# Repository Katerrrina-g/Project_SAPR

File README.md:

# Отчет по Домашнему заданию: Разработка печатной платы блока питания
**Выполнила: Генина Е.И.**
**Группа: БМТ2-31М**
**Дисциплина: САПР электронных стредств**
Среда разработки: KiCad 10.0

**1. Описание проекта**
В рамках данного проекта была разработана печатная плата блока питания. Устройство предназначено для питания электроимпедансного томографа для функциональной диагностики мышц.
На вход платы подается неразвязанное напряжение +5В (от внешнего источника питания, например, от ноутбука). С помощью рассматриваемой схемы генерируются следующие выходные напряжения:

+3.3В (для цифровых цепей);
+5В (развязанное для аналоговых цепей);
+15В и -15В (для аналоговых цепей).

Основу схемы составляют преобразователи и регуляторы напряжения:

ADP5071 — двухканальный DC-DC преобразователь с генерацией положительного и отрицательного напряжений.

ISOUSB211 — изолированный повторитель USB 2.0 (обеспечивает развязку).

TPS7A49 и TPS7A30 — малошумящие линейные регуляторы для формирования напряжений +15В и -15В.

**2. Библиотека компонентов и Git-сабмодуль**
Библиотека компонентов была вынесена в отдельный репозиторий и подключена к основному проекту как git-сабмодуль. Это обеспечивает независимое версионирование и переиспользование.

Символы (УГО): Файл UGO.kicad_sym. УГО оформлены по ГОСТ.

Посадочные места: Папка SAPR.pretty.

Партномеры: В свойствах каждого компонента заполнено поле Manufacturer_Part_Number с партномерами.

Пути: В настройках KiCad используются относительные пути с применением переменной ${KIPRJMOD} (${KIPRJMOD}/libs/kicad-library/UGO.kicad_sym;${KIPRJMOD}/libs/kicad-library/SAPR.pretty).

Все посадочные места были проверены на соответствие даташитам. Для стандартных компонентов (резисторы, конденсаторы) использовались стандартные футпринты, для специфических — специализированные из базы производителя, отстутствующие посадочные места были созданы самостоятельно. 3D-модели привязаны и корректно отображаются.

**3. Принципиальная схема (Э3)**
Схема электрическая принципиальная оформлена на листе формата А3 согласно ГОСТ.

Классы цепей: Был создан класс Power (фиолетовый цвет, стиль линии — штрихи). В этот класс включены все цепи питания. Остальные цепи относятся к классу Default.

Ширина дорожек для класса Power задана как 0.4 мм, однако при трассировке преимущественно использовались полигоны (зоны).

**4. Файл печатной платы**
Плата спроектирована в 4 слоя с учетом технологических ограничений производства «Резонит».

Стек слоев (Board Stackup):
F.Cu (Верхний слой) — 0.035 мм
Диэлектрик 1 (Prepreg) — 0.1 мм
In1.Cu (Внутренний 1) — 0.035 мм
Диэлектрик 2 (Ядро, FR4) — 1.24 мм
In2.Cu (Внутренний 2) — 0.035 мм
Диэлектрик 3 (Prepreg) — 0.1 мм
B.Cu (Нижний слой) — 0.035 мм

Технологические нормы (Constraints):
Minimum clearance (Мин. зазор)	0.20 мм

Copper to edge clearance (Зазор от меди до края) 0.50 мм

Minimum track width (Мин. ширина дорожки) 0.20 мм

Minimum annular width (Мин. кольцо меди) 0.15 мм

Minimum drill size (Мин. диаметр сверления)	0.30 мм

Hole to hole distance (Расстояние между отверстиями)	0.20 мм

Copper to hole clearance (Зазор медь-отверстие)	0.25 мм

Minimum text height (Мин. высота текста)	1.0 мм

Minimum text thickness (Мин. толщина линии)	0.15 мм

Silk to soldermask clearance (Зазор шелкография-маска)	0.10 мм

Soldermask expansion (Расширение маски)	0.05 мм

Minimum connection width (Мин. ширина соединения)	0.20 мм

Thermal relief spoke count (Кол-во спиц развязки)	4

Зазор медь-край платы: 0.4 мм

Использованы переходные отверстия диаметром 0,3/0.6 мм (со сверлом 0.3 мм).

**5. Автоматизация сборки**
Для автоматизации процесса проверки и подготовки производственных файлов в корне проекта (путь D:\Univ\САПР ЭС\Project_sapr) расположен скрипт build.bat.

Скрипт использует утилиту kicad-cli и выполняет следующие действия:

ERC — Проверка электрических правил схемы (учитывает предупреждения).

DRC — Проверка правил проектирования печатной платы (учитывает предупреждения).

Gerber + Excellon — Генерация файлов для производства.

BOM — Генерация перечня элементов в формате CSV.

PDF — Экспорт схемы в PDF.

**6. Инструкция по развертыванию проекта**
Для того чтобы скачать проект вместе с библиотекой, необходимо использовать следующую команду:

git clone --recursive https://github.com/Katerrrina-g/Project_SAPR.git

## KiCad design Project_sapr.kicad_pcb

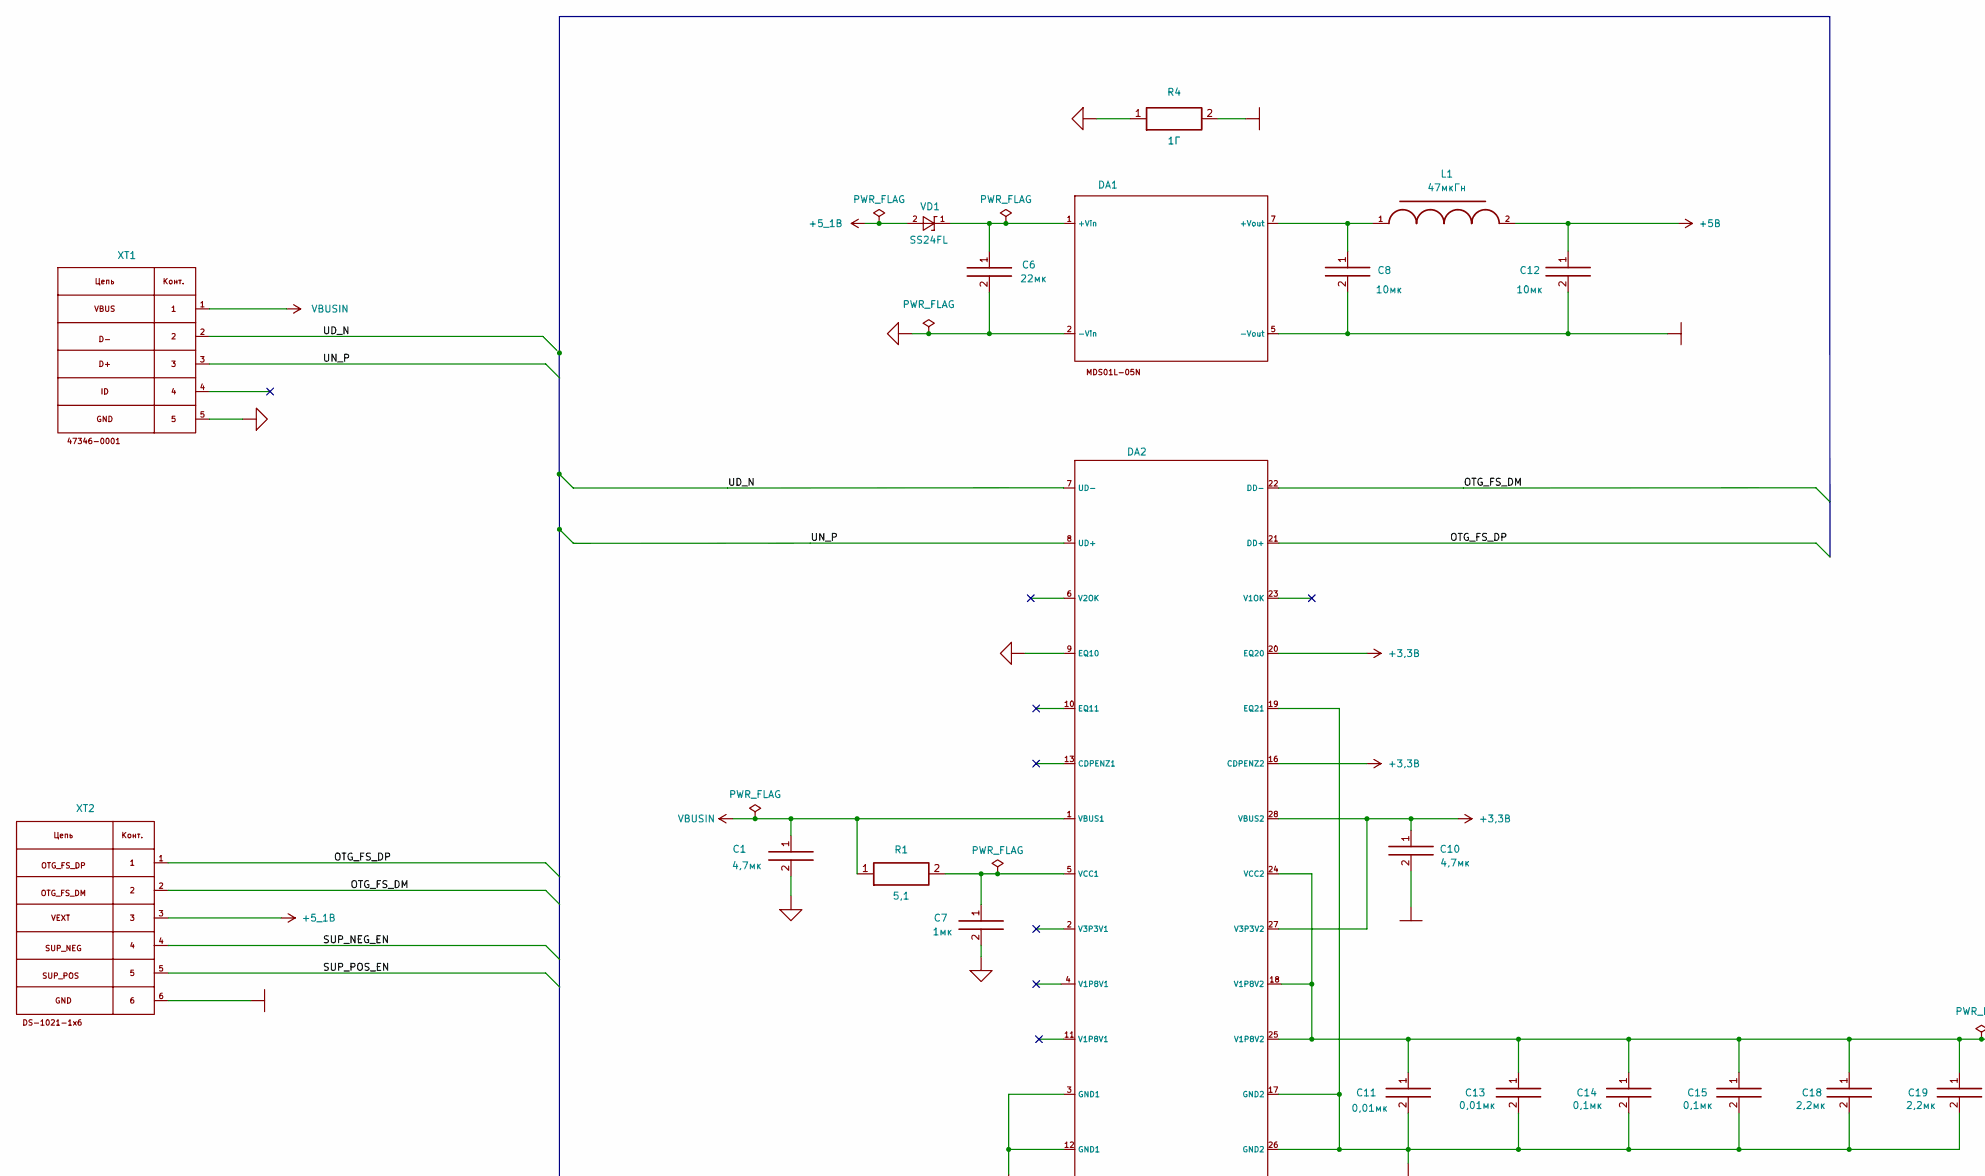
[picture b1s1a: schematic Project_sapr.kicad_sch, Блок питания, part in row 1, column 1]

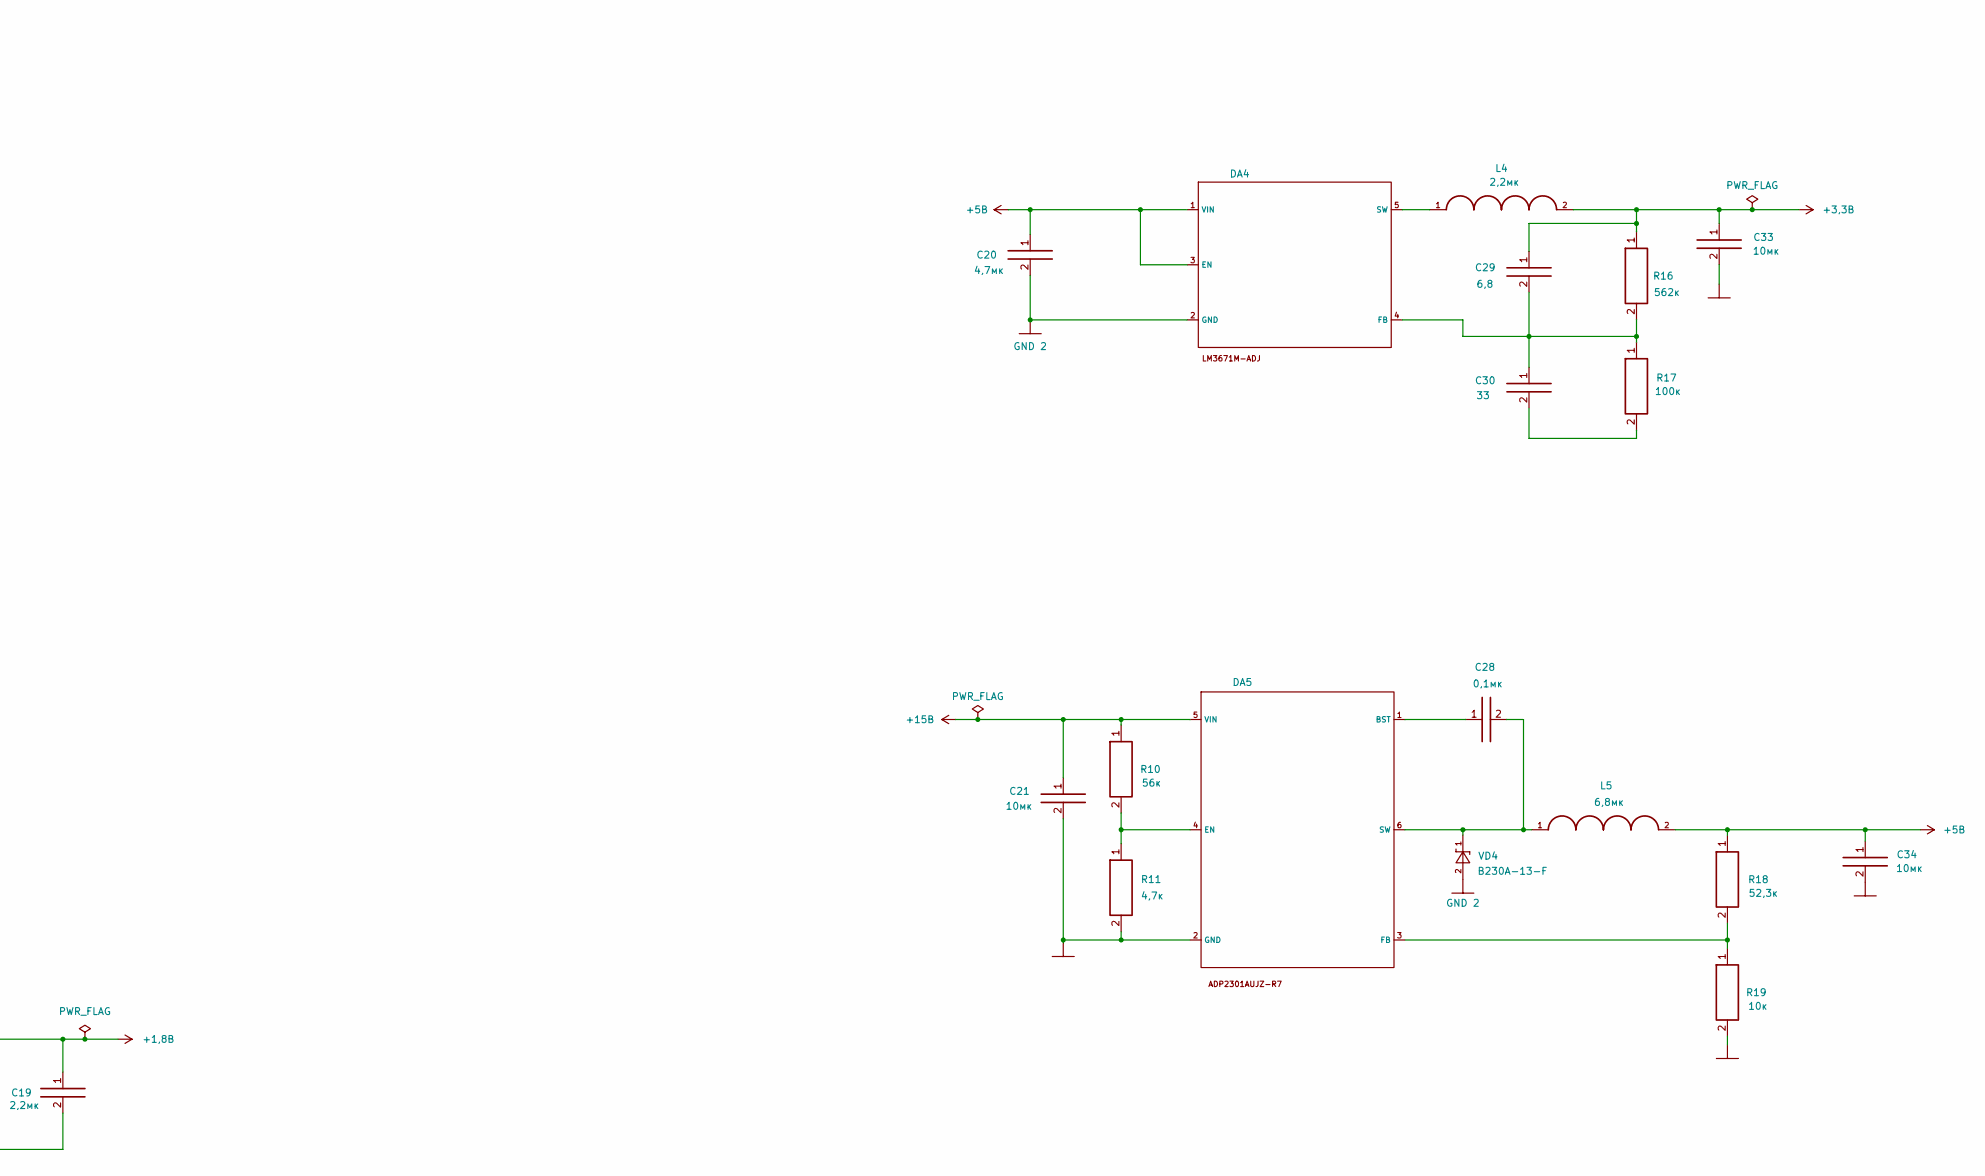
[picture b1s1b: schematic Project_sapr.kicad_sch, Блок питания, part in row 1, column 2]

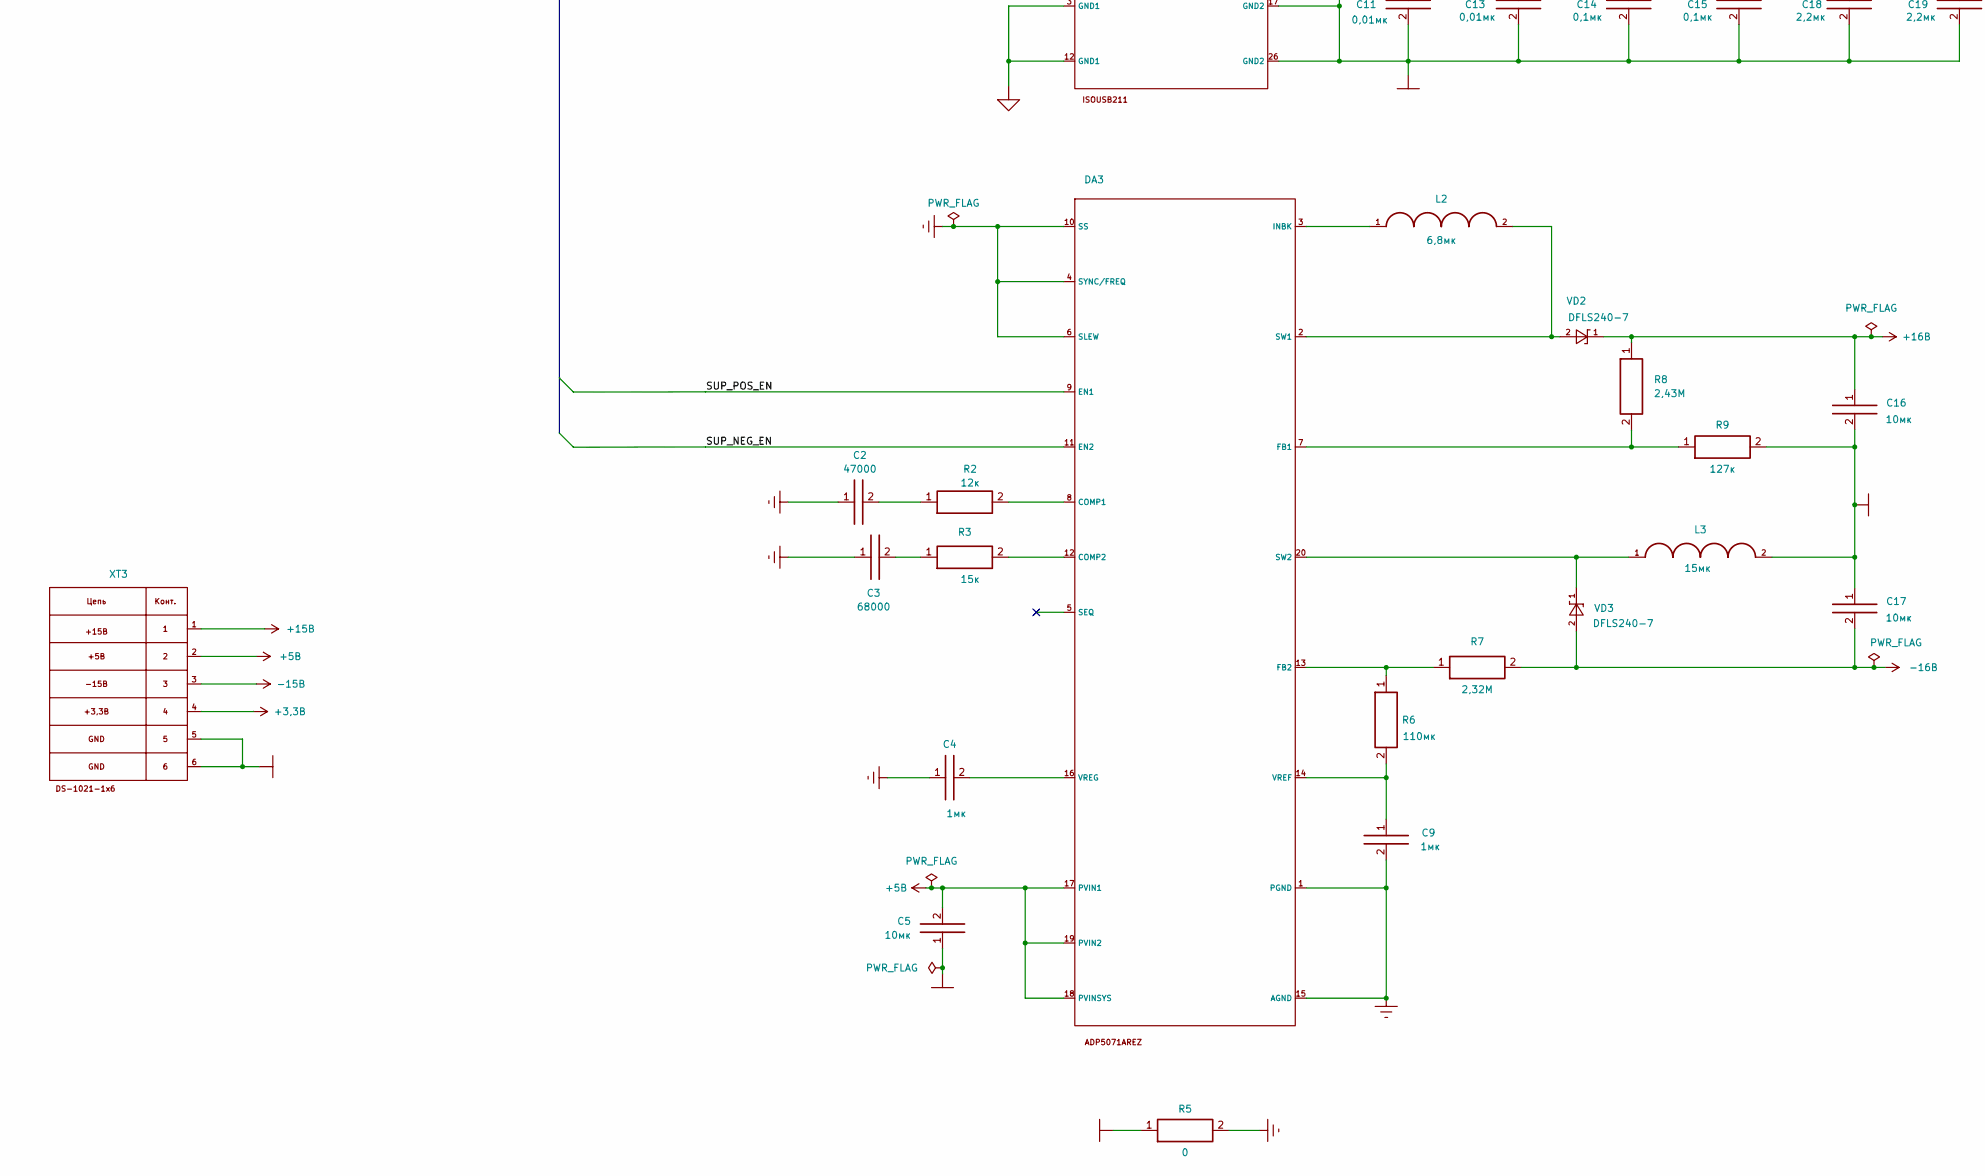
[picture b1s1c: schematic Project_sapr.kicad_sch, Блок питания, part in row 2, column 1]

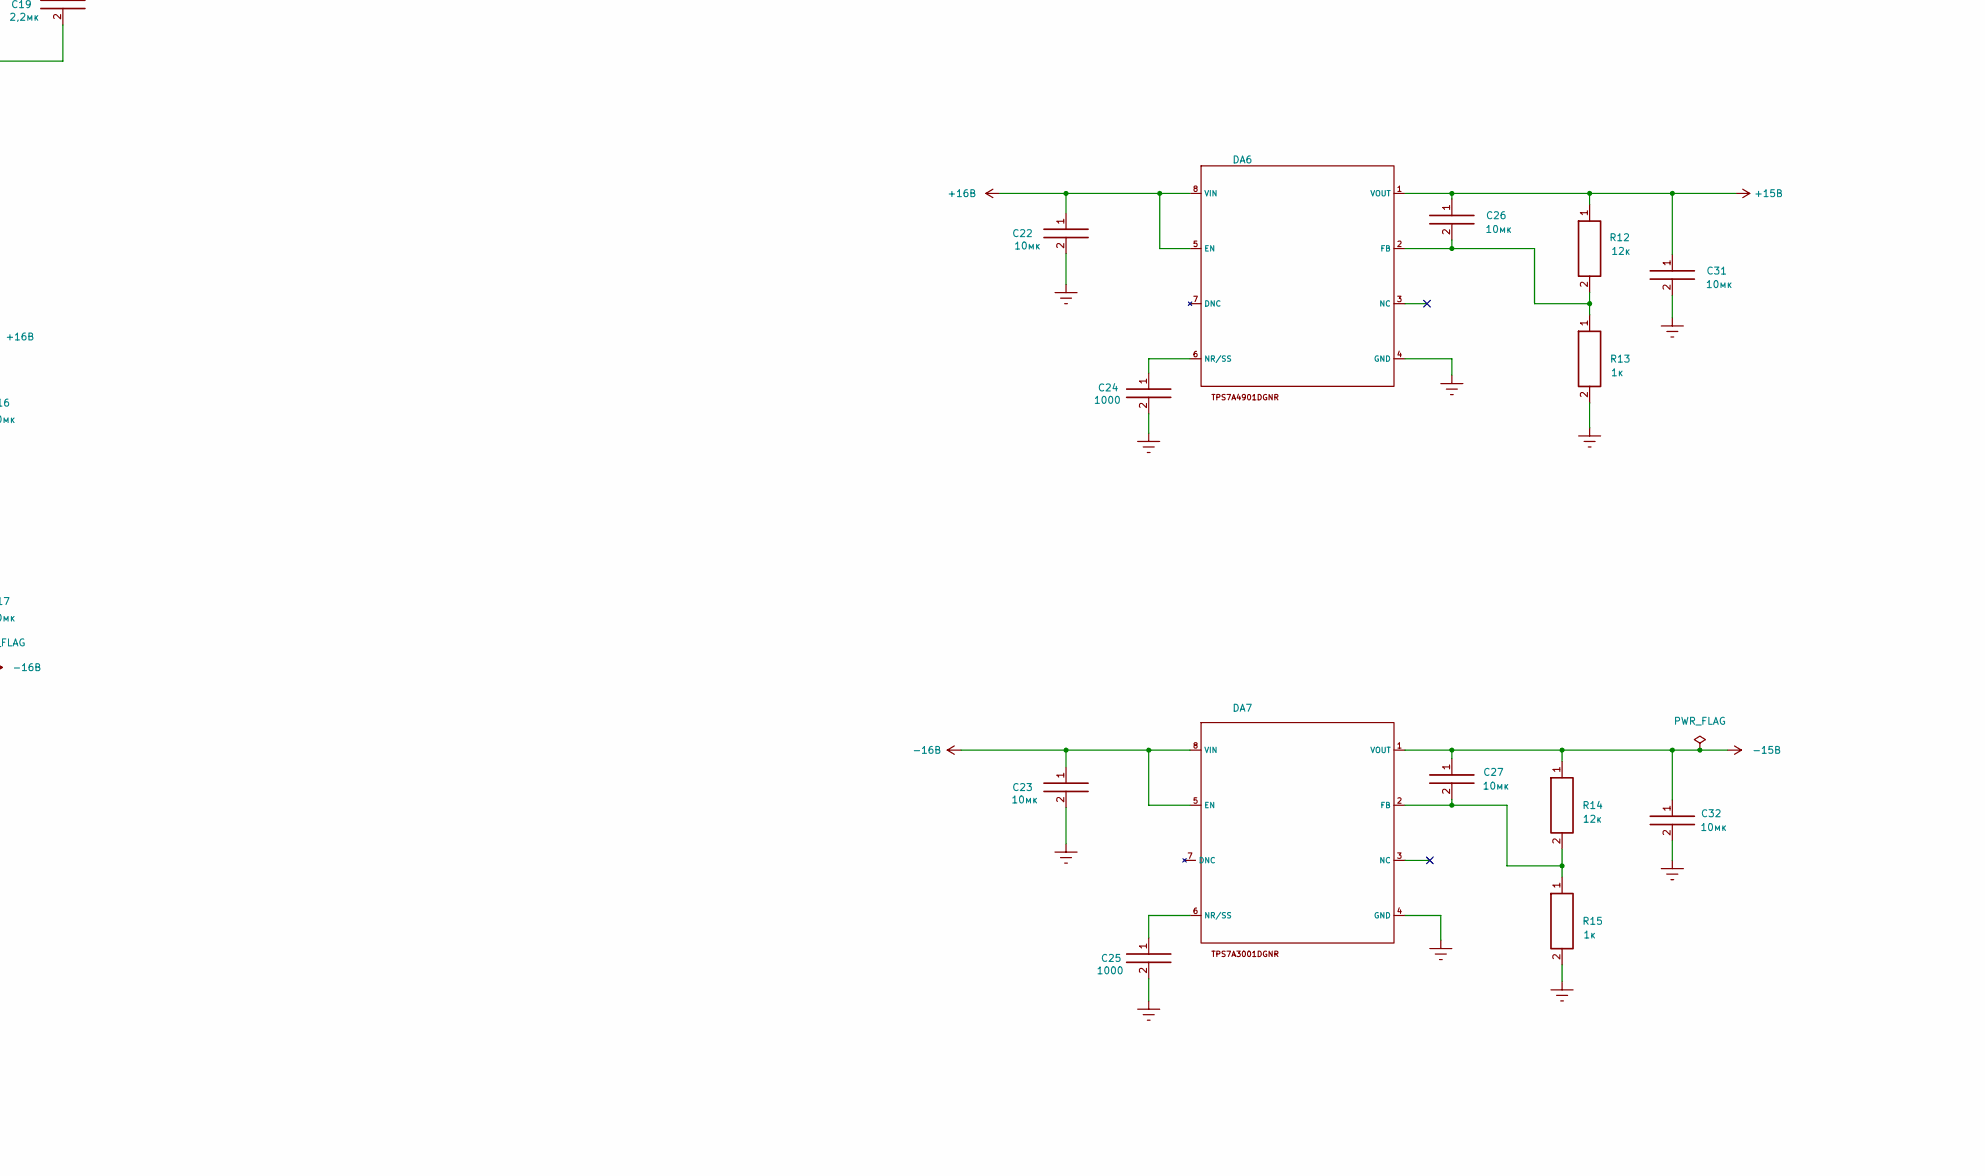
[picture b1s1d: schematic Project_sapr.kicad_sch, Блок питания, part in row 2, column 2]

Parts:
C1, C10, C20: 4,7мк; C_0201_0603Metric; Manufacturer_Part_Number GRM188Z71C475KE21D
C2: 47000; C_0201_0603Metric; Manufacturer_Part_Number GCJ188R71E473KA01D
C3: 68000; C_0201_0603Metric; Manufacturer_Part_Number GRM188R71H683KA93D
C4, C7, C9: 1мк; C_0201_0603Metric; Manufacturer_Part_Number GRM033R60J105MEA2D
C5, C8, C21, C26, C27, C34: 10мк; C_0402_1005Metric; Manufacturer_Part_Number CC0402MRX5R6BB106
C6: 22мк; C_0402_1005Metric; Manufacturer_Part_Number GRM155R60J226ME11D
C11, C13: 0,01мк; C_0201_0603Metric; Manufacturer_Part_Number GRM033R71E103KE14D
C12: 10мк; R_0402_1005Metric; Manufacturer_Part_Number CC0402MRX5R6BB106
C14, C15, C28: 0,1мк; C_0201_0603Metric; Manufacturer_Part_Number GRM033Z71C104KE14D
C16, C17: 10мк; C_1210_3225Metric; Manufacturer_Part_Number GRM32ER71H106KA12L
C18, C19: 2,2мк; C_0201_0603Metric; Manufacturer_Part_Number GRM188R71A225KE15D
C22, C23, C31, C32: 10мк; C_1206_3216Metric; Manufacturer_Part_Number GRM31CR61H106KA12L
C24, C25: 1000; C_0402_1005Metric; Manufacturer_Part_Number GCM155R71H102KA37J
C29: 6,8; C_0402_1005Metric; Manufacturer_Part_Number CC0402CRNPO9BN6R8
C30: 33; C_0402_1005Metric; Manufacturer_Part_Number GRM1555C1H330J
C33: 10мк; C_0805_2012Metric; Manufacturer_Part_Number GRM21BR60J106K
DA1: MDS01L-N; Manufacturer_Part_Number MDS01L-05N
DA2: ISOUSB211; SSOP-28-ISOUSB211; Manufacturer_Part_Number ISOUSB211DPR
DA3: ADP5071AREZ; TSSOP-20_4.4x6.5mm_P0.65mm; Manufacturer_Part_Number ADP5071AREZ
DA4: LM3671MF-ADJ; SOT-23-5; Manufacturer_Part_Number LM3671MF-ADJ
DA5: ADP2301AUJZ-R7; TSOT-23-6
DA6: TPS7A4901DGNR; MSOP-8-1EP_3x3mm_P0.65mm_EP1.95x2.15mm; Manufacturer_Part_Number TPS7A4901DGNR
DA7: TPS7A3001DGNR; MSOP-8-1EP_3x3mm_P0.65mm_EP1.95x2.15mm; Manufacturer_Part_Number TPS7A3001DGNR
L1: 47мкГн; L_TDK_NLV32_3.2x2.5mm; Manufacturer_Part_Number NLCV32T-470K-EF
L2, L5: 6,8мк; L_0201_0603Metric; Manufacturer_Part_Number MLF1608E6R8KTD25
L3: 15мк; L_0201_0603Metric; Manufacturer_Part_Number MLF1608C150KTA00
L4: 2,2мк; L_0201_0603Metric; Manufacturer_Part_Number ILSB0603ER2R2K
R1: 5,1; R_0402_1005Metric; Manufacturer_Part_Number RC0402FR-075R1L
R2, R12, R14: 12к; R_0402_1005Metric; Manufacturer_Part_Number RC0402FR-0712KL
R3: 15к; R_0402_1005Metric; Manufacturer_Part_Number RC0402FR-0715RL
R4: 1Г; R_1206_3216Metric; Manufacturer_Part_Number CRHV1206AF1G00FKET
R5: 0; R_0201_0603Metric; Manufacturer_Part_Number RC0201FR-070RL
R6: 110мк; R_0402_1005Metric; Manufacturer_Part_Number RC0402FR-07110KL
R7: 2,32М; R_0805_2012Metric; Manufacturer_Part_Number RC0805FR-072M32L
R8: 2,43М; R_0805_2012Metric; Manufacturer_Part_Number RC0805FR-072M43L
R9: 127к; R_0402_1005Metric; Manufacturer_Part_Number RC0402FR-07127KL
R10: 56к; R_0402_1005Metric; Manufacturer_Part_Number RC0402FR-0756KL
R11: 4,7к; R_0402_1005Metric; Manufacturer_Part_Number RC0402FR-074K7L
R13, R15: 1к; R_0402_1005Metric; Manufacturer_Part_Number RC0402FR-071KL
R16: 562к; R_0402_1005Metric; Manufacturer_Part_Number RC0402FR-07562K
R17: 100к; R_0402_1005Metric; Manufacturer_Part_Number RC0402FR-07100KL
R18: 52,3к; R_0402_1005Metric; Manufacturer_Part_Number RC0402FR-0752K3L
R19: 10к; R_0402_1005Metric; Manufacturer_Part_Number RC0402FR-0710KL
VD1: SS24FL; Manufacturer_Part_Number SS24FL
VD2, VD3: DFLS240-7; D_PowerDI-123; Manufacturer_Part_Number DFLS240-7
VD4: B230A-13-F; D_SMA; Manufacturer_Part_Number B230A-13-F
XT1: USB_Micro-B_Molex_47346-0001
XT2, XT3: (no value)

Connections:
+1,8B: C11.1, C13.1, C14.1, C15.1, C18.1, C19.1, DA2.18 (V1P8V2), DA2.24 (VCC2), DA2.25 (V1P8V2)
+3,3B: C10.1, C29.1, C33.1, DA2.16 (CDPENZ2), DA2.20 (EQ20), DA2.27 (V3P3V2), DA2.28 (VBUS2), L4.2, R16.1, XT3.4
+5B: C5.2, C12.1, C20.1, C34.1, DA3.17 (PVIN1), DA3.18 (PVINSYS), DA3.19 (PVIN2), DA4.1 (VIN), DA4.3 (EN), L1.2, L5.2, R18.1, XT3.2
+5_1B: VD1.2, XT2.3
+15B: C21.1, C26.1, C31.1, DA5.5 (VIN), DA6.1 (VOUT), R10.1, R12.1, XT3.1
+16B: C16.1, C22.1, DA6.5 (EN), DA6.8 (VIN), R8.1, VD2.1
-15B: C27.1, C32.1, DA7.1 (VOUT), R14.1, XT3.3
-16B: C17.2, C23.1, DA7.5 (EN), DA7.8 (VIN), R7.2, VD3.2
/OTG_FS_DM: DA2.22 (DD-), XT2.2
/OTG_FS_DP: DA2.21 (DD+), XT2.1
/SUP_NEG_EN: DA3.11 (EN2), XT2.4
/SUP_POS_EN: DA3.9 (EN1), XT2.5
/UD_N: DA2.7 (UD-), XT1.2
/UN_P: DA2.8 (UD+), XT1.3
GND 1: C1.2, C6.2, C7.2, DA1.2 (-Vin), DA2.3 (GND1), DA2.9 (EQ10), DA2.12 (GND1), R4.1, XT1.5
GND 2: C5.1, C8.2, C10.2, C11.2, C12.2, C13.2, C14.2, C15.2, C16.2, C17.1, C18.2, C19.2, C20.2, C21.2, C33.2, C34.2, DA1.5 (-Vout), DA2.17 (GND2), DA2.19 (EQ21), DA2.26 (GND2), DA4.2 (GND), DA5.2 (GND), L3.2, R4.2, R5.1, R9.2, R11.2, R19.2, VD4.2, XT2.6, XT3.5, XT3.6
GND 3: C2.1, C3.1, C4.1, C9.2, C22.2, C23.2, C24.2, C25.2, C31.2, C32.2, DA3.1 (PGND), DA3.4 (SYNC/FREQ), DA3.6 (SLEW), DA3.10 (SS), DA3.15 (AGND), DA6.4 (GND), DA7.4 (GND), R5.2, R13.2, R15.2
unnamed: C2.2, R2.1
unnamed: C3.2, R3.1
unnamed: C30.2, R17.2
unnamed: C6.1, DA1.1 (+Vin), VD1.1
unnamed: C8.1, DA1.7 (+Vout), L1.1
unnamed: C7.1, DA2.5 (VCC1), R1.2
unnamed: DA3.8 (COMP1), R2.2
unnamed: DA3.12 (COMP2), R3.2
unnamed: DA3.7 (FB1), R8.2, R9.1
unnamed: DA3.13 (FB2), R6.1, R7.1
unnamed: DA3.3 (INBK), L2.1
unnamed: DA3.2 (SW1), L2.2, VD2.2
unnamed: DA3.20 (SW2), L3.1, VD3.1
unnamed: C9.1, DA3.14 (VREF), R6.2
unnamed: C4.2, DA3.16 (VREG)
unnamed: C29.2, C30.1, DA4.4 (FB), R16.2, R17.1
unnamed: DA4.5 (SW), L4.1
unnamed: C28.1, DA5.1 (BST)
unnamed: DA5.4 (EN), R10.2, R11.1
unnamed: DA5.3 (FB), R18.2, R19.1
unnamed: C28.2, DA5.6 (SW), L5.1, VD4.1
unnamed: C26.2, DA6.2 (FB), R12.2, R13.1
unnamed: C24.1, DA6.6 (NR/SS)
unnamed: C27.2, DA7.2 (FB), R14.2, R15.1
unnamed: C25.1, DA7.6 (NR/SS)
VBUSIN: C1.1, DA2.1 (VBUS1), R1.1, XT1.1

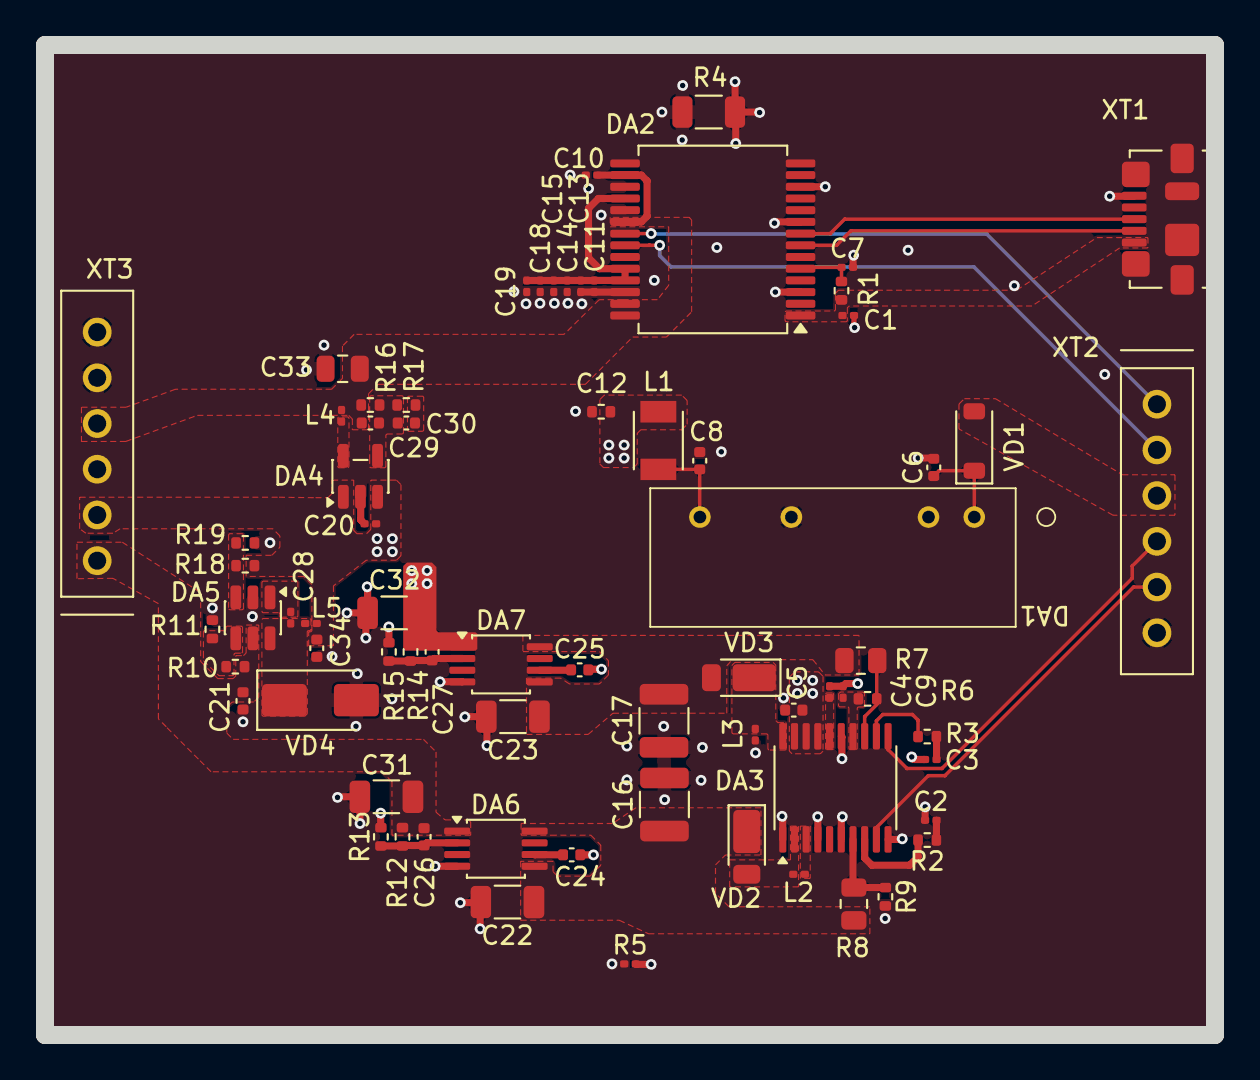
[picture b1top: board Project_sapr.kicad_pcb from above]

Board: 4 copper layers, 65.0 x 55.0 mm, 72 parts (0 on the bottom side), 43 nets.
